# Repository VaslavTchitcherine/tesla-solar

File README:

TESLA MODULE SOLAR POWER SYSTEM

This describes how to use Tesla Model S battery modules in an offgrid
solar power system, comprised of:

1) Any number (between 1 and 63) of Tesla Model S battery modules connected in parallel.
The prototype system has two modules from a P100D, each 6.4 kWh. 

2) A solar charge controller.
Victron BlueSolar 24V MPPT 100/50 Charge Controller (100V, 50A maximum input).
It is essential that the controller allows you to set the maximum charge voltage
to something suitable for the Tesla modules (i.e. never more than 25.2V).

3) An inverter for AC output.  Modern pure sine wave inverters
are quite efficient.  Ideally you want one with an adjustable
(or no) low voltage cutoff, as the Tesla modules are usable down to about 18V,
lower than many other battery chemistries.

4) Two hall effect current sensors (Allegro ACS758) to measure panel
current and battery current.  The battery current can be positive or negative,
depending on whether the battery is charging or discharging.  Panel current
is never less than zero.

5) A pair of DC solid state relays (Crydom D06D100) to disconnect the panels
if the battery modules are overvoltage, and disconnect the battery modules if they
are undervoltage.

6) A Raspberry Pi Zero W with a custom Pi hat.  Python code on the Pi:
	a) Communicates with the Tesla modules using a 612500 baud serial loop.
	b) Reads current sensors using a 16 bit dual A/D (ADS1115)
	c) Monitors and logs voltages, currents, and battery temperatures.
	d) Serves plots of the logs on a web page (using the dygraphs.js library)
	d) Controls the SSR disconnects via GPIO
	e) Balances batteries at both the module and cell level, by switching in
	   shunt resistors on the Tesla BMS boards when necessary.

7) Optionally, an AC SSR (Opto22 240A45) to disconnect the output of the 
inverter from the load.  Some inverters enter an error state if there
is an AC load when DC input power is applied.  This SSR disconnects the
load from the output of the inverter until several seconds after the
inverter is connected to the battery bank by the respective DC SSR.

The Pi is powered directly (through a small fuse) from the
battery modules, using an LM2596-based buck converter.
It is important that the Pi remain powered through
an undervoltage condition, so that it can close the SSR to reconnect the
battery modules to the inverter once they are sufficiently charged so that
they are no longer undervoltage. 

(BLOCK DIAGRAM)
(PHOTOS of system and control box)

Tesla Battery Modules
---------------------

All Telsa Model S battery modules have 6 series-connected groups
of a large number of 18650 LiOn cells in parallel.
For example, the P100D module has 516 18650 LiOn cells per module, connected 6s86p.

A fully charged 18650 cell is 4.2V, so 4.2*6 = 25.2V is the maximum voltage
of a fully charged module.  It is better to set the float voltage on the
Victon charge controller for a lower voltage (e.g. 24.2V) to both
allow some headroom for unbalanced cells and to avoid stressing the cells.
The Panasonic NCR18650B data sheet shows a knee at around 3.0V on the
discharge characteristics graph, so 3.0*6 = 18V can be considered the minimum usable voltage of a module.

The Tesla module has a BMS board, containing:
C8051F536 microprocessor
Silicon Labs 8642ED RF isolator
TI BQ76PL536A Lithium ion battery monitor (for 6 cells)
158 ohm resistors, 4 in parallel, for a 39.5 ohms of bleed for balancing

These modules communicate via 612500 baud serial, with the serial connection
arranged in a loop (Wiring2.png).  What is meant by a loop?
Each module receives serial data on RX (pin 2) and transmits it on TX (pin 4).
There are two separate channels that are not connected to each other.
So any data intended for the entire system goes to the first module, which then retransmits it
from its TX to the input RX on the next module in the chain.

Connectors for Tesla modules are:
	Molex 15-97-5101 CONN RCPT 10POS DUAL MINI-FIT (Digikey WM4772-ND)
and the pins are:
	Molex 39-00-0038 CONN TERM FEMALE 18-24AWG TIN (Digikey WM2501CT-ND)

Using the Raspberry Pi (Pi Zero W, Pi3, Pi3B+) UART
---------------------------------------------------

UART0_TXD is GPIO 14, pin 8 on GPIO header
UART0_RXD is GPIO 15, pin 10 on GPIO header

By default the the primary UART (/dev/serial0) is used for a console.
Use the raspi-config utility to disable this.
Select option 5, Interfacing options, then option P6, Serial, and select No.

The BCM2837 on a recent Pi has two UARTS, but the mini UART is not suitable for
high speed serial communication, having too small a buffer and variable frequency.
To use the PL011 UART instead of the mini UART, add these lines to the /boot/config.txt file:
        dtoverlay=pi3-disable-bt
        enable_uart=1
This disables the Bluetooth module and maps the PL011 UART onto GPIO pins 14 and 15,
which appears as /dev/serial0 (a symbolic link to /dev/ttyAMA0).
Note the pi4 instructions are different:
https://di-marco.net/blog/it/2020-06-06-paspberry_pi_3_4_and_0_w_serial_port_usage/

Also, the Pi is 3.3V, and needs to interface to 5V RS232 serial levels on the Tesla modules.
For this, we use the circuit from the SparkFun bidirectional logic level converter
(https://www.sparkfun.com/products/12009) which uses a BSS138 MOSFET with pullups to
perform the level conversion.

References:
https://www.raspberrypi.org/documentation/configuration/uart.md
https://raspberrypi.stackexchange.com/questions/45570/how-do-i-make-serial-work-on-the-raspberry-pi3-pi3b-pizerow

A/D conversion
--------------

To use the ADS1115, the I2C interface has to be enabled on the Pi.
Details on how do do this using raspi-config are here:
    https://learn.adafruit.com/adafruits-raspberry-pi-lesson-4-gpio-setup/configuring-i2c

We use the Adafruit_ADS1x15 library to communicate with the ADS1115:
	sudo apt-get update
	sudo apt-get install -y python-smbus
	sudo apt-get install i2c-tools
	sudo apt-get install build-essential python-dev python-smbus git
	cd ~
	git clone https://github.com/adafruit/Adafruit_Python_ADS1x15.git
	cd Adafruit_Python_ADS1x15
	sudo python setup.py install

See:
	https://learn.adafruit.com/adafruit-4-channel-adc-breakouts
	https://github.com/adafruit/Adafruit_Python_ADS1X15
	https://learn.adafruit.com/raspberry-pi-analog-to-digital-converters/ads1015-slash-ads1115

DCDC SSR Disconnects
--------------------

A Crydom D06D100 DCDC solid state relay disconnects the panels if an overvoltage condtion
should occur (e.g. misconfiguration or failure of the charge controller).
And another D06D100 is used to disconnect the Tesla modules if an undervoltage condtion
should occur (e.g. too much power consumption or insufficient sunshine).

The SSRs dissipate less power than would
mechanical contactors, except briefly during infrequent conditions of very high current draw.

A mechanical contactor such as a Gigavac of suitable current capacity draws 0.28 A for a
24 VDC coil voltage, i.e. 6.7 W at all times.
With 0.005 ohm Rds(on) the Crydom D06D100 SSR relay at draws
	I^2R = 100 * 100 * 0.005 = 12.5 W
at 100A.  But in practice I never pull more than 40A from my batteries,
and generally only a few amps.   So this Crydom DC SSR (which I
understand to be a pair of mosfets with optoisolated driver in a
convenient package) wastes less power than keeping the electromagnet for
a contactor powered.

Note that the Crydom D06D100 is expensive, but I would not trust a
(possibly counterfeit) Fotek to handle the current.

Battery Balancing
-----------------

Despite widespread disinformation and confusion on the subject, battery
balancing is simple.

The Tesla BMS board has shunt resistors, one per cell, which can be independently switched in to 
bleed charge from any of the 6 cells in a battery module.   This "top balancing" should be done whenever
any cell's voltage is sufficiently much higher than that of the second
highest cell in the module.

Analogously, at a module level, all 6 bleed resistors for a module should be
switched in when the voltage for that module is sufficiently much higher than that of the second
highest module.

This balancing is performed by the Python code, voltage thesholds for balancing are
parameters stored in global variables.

Logging and Plotting
--------------------

The Python code writes 3 log files, the names of which must be supplied as positional
command line parameters.

This first of these log files is a CSV file, fields of which are respectively:
datetime in ISO format (YYYY-MM-DD HH:MM:SS)
	module 1 Soc (%)
	module 1 Voltage (V)
	module 1 Temperature 1 (degrees C)
	module 1 Temperature 2 (degrees C)
	module 1 maximum cell imbalance (V)
	module 2 Soc (%)
	module 2 Voltage (V)
	module 2 Temperature 1 (degrees C)
	module 2 Temperature 2 (degrees C)
	module 2 maximum cell imbalance (V)
	.
	.
	.
		module n Soc (%)
	module n Voltage (V)
	module n Temperature 1 (degrees C)
	module n Temperature 2 (degrees C)
	module n maximum cell imbalance (V)
	battery current (A)
	panel current (A)

The second log file is blank delimited file, with a timestamp and fields for the voltage of each cell.

The third log file contains warnings, such as over and undervoltage conditions.

Plots of fields the first log file can be made using the dygraphs.js library (http://dygraphs.com).
Specify /var/www/html/log.csv as the first command line argument to tesla.py and use
index.html as the home page.

Here is sample output.
You can see I had 3 espressos today.

Pi Hat
------

Eagle files and BOM with Digikey part numbers for the Pi Hat.

Thanks
------

Thanks to everyone who did the hard work of reverse engineering the Tesla modules, and
to Ulrich Gall for the original Python code.
http://evtv.me/2017/03/tesla-battery-victory-lap/
https://github.com/collin80/TeslaBMS
https://github.com/jarrod89/TeslaBMS
https://github.com/tomdebree/TeslaBMS

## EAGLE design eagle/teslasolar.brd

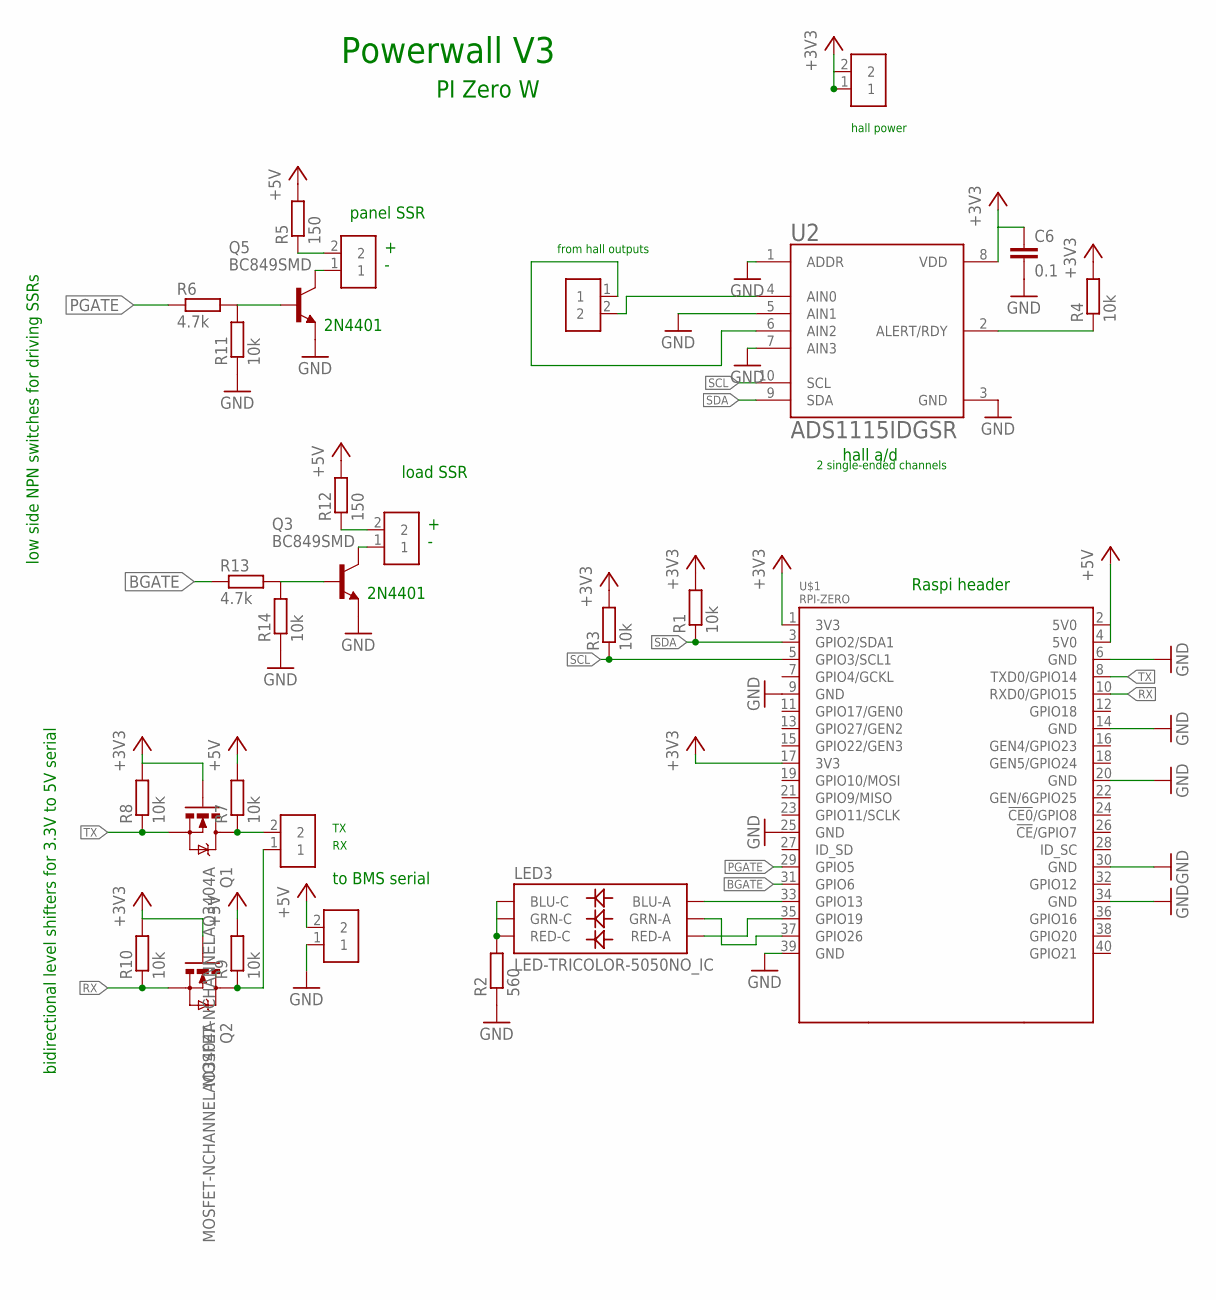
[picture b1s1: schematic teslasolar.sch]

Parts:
C6: 0.1; C0603
J1, J2, J3, J4, J5, J6: 282834-2; CONN_282834-2
LED3: LED-TRICOLOR-5050NO_IC; LED-TRICOLOR-5050
Q1, Q2: MOSFET-NCHANNELAO3404A; SOT23-3
Q3, Q5: BC849SMD; SOT23-BEC
R1, R3, R4, R7, R8, R9, R10, R11, R14: 10k; R0603
R2: 560; R0805
R5, R12: 150; R0603
R6, R13: 4.7k; R0603
U2: ADS1115IDGSR; SOP50P490X110-10N
U$1: RPI-ZERO; RASPBERRYPI_BASTELSTUBE_V13_RASPI_BOARD_B+_FULL

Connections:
3V3@2: U$1.17 (3V3)
+3V3: C6.1, J4.1, J4.2, Q1.1 (G), Q2.1 (G), R1.2, R3.2, R4.2, R8.2, R10.2, U2.8 (VDD), U$1.1 (3V3)
+5V: J5.2, R5.2, R7.2, R9.2, R12.2, U$1.2 (5V0), U$1.4 (5V0)
BGATE: R13.1, U$1.31 (GPIO6)
GND: C6.2, J5.1, Q3.E, Q5.E, R2.1, R11.1, R14.1, U2.1 (ADDR), U2.3 (GND), U2.5 (AIN1), U2.7 (AIN3), U$1.6 (GND), U$1.9 (GND), U$1.14 (GND), U$1.20 (GND), U$1.25 (GND), U$1.30 (GND), U$1.34 (GND), U$1.39 (GND)
unnamed: LED3.3 (BLU-A), U$1.33 (GPIO13)
unnamed: LED3.2 (RED-A), U$1.35 (GPIO19)
unnamed: LED3.1 (GRN-A), U$1.37 (GPIO26)
unnamed: LED3.4 (BLU-C), LED3.5 (RED-C), LED3.6 (GRN-C), R2.2
unnamed: J3.2, Q1.3 (D), R7.1
unnamed: J3.1, Q2.3 (D), R9.1
unnamed: J1.2, R5.1
unnamed: J6.2, R12.1
unnamed: J1.1, Q5.C
unnamed: Q5.B, R6.2, R11.2
unnamed: J6.1, Q3.C
unnamed: Q3.B, R13.2, R14.2
unnamed: R4.1, U2.2 (ALERT/RDY)
unnamed: J2.1, U2.6 (AIN2)
unnamed: J2.2, U2.4 (AIN0)
PGATE: R6.1, U$1.29 (GPIO5)
RX: Q2.2 (S), R10.1, U$1.10 (RXD0/GPIO15)
SCL: R3.1, U2.10 (SCL), U$1.5 (GPIO3/SCL1)
SDA: R1.1, U2.9 (SDA), U$1.3 (GPIO2/SDA1)
TX: Q1.2 (S), R8.1, U$1.8 (TXD0/GPIO14)

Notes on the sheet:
hall a/d
PI Zero W
to BMS serial
2 single-ended channels
from hall outputs
hall power
Raspi header
panel SSR
Powerwall V3
2N4401
bidirectional level shifters for 3.3V to 5V serial
low side NPN switches for driving SSRs
load SSR

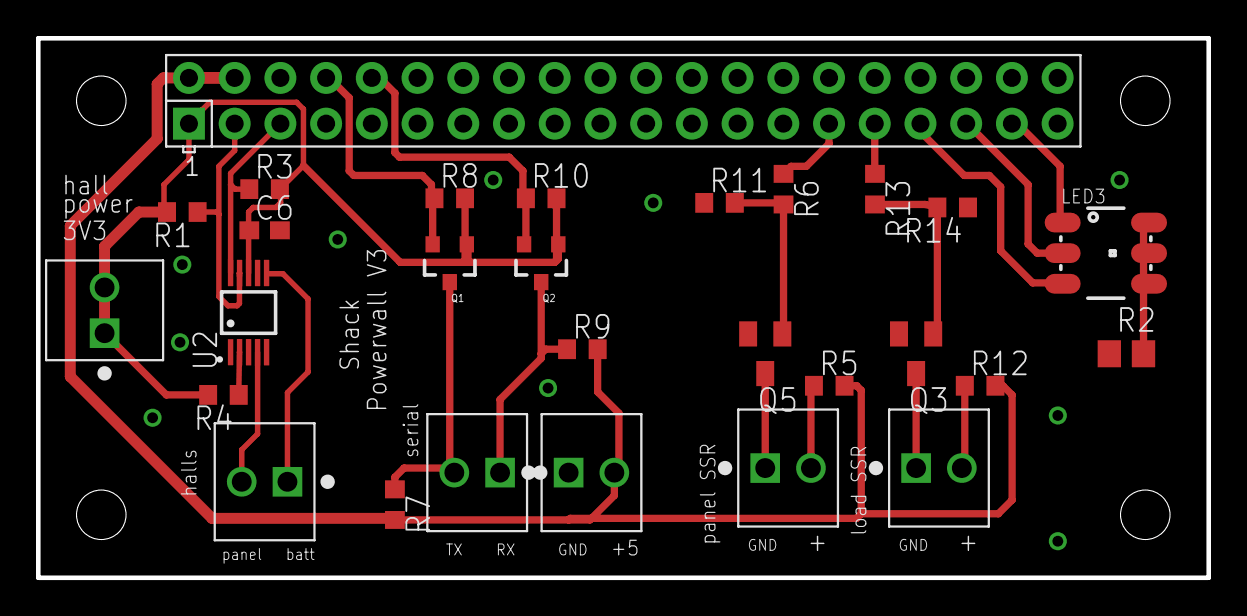
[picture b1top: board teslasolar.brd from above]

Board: 2 copper layers, 65.0 x 30.0 mm, 28 parts (0 on the bottom side), 24 nets.

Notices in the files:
parts and their libraries:
SparkFun-LED: Licensing: Creative Commons ShareAlike 4.0 International - https://creativecommons.org/licenses/by-sa/4.0
